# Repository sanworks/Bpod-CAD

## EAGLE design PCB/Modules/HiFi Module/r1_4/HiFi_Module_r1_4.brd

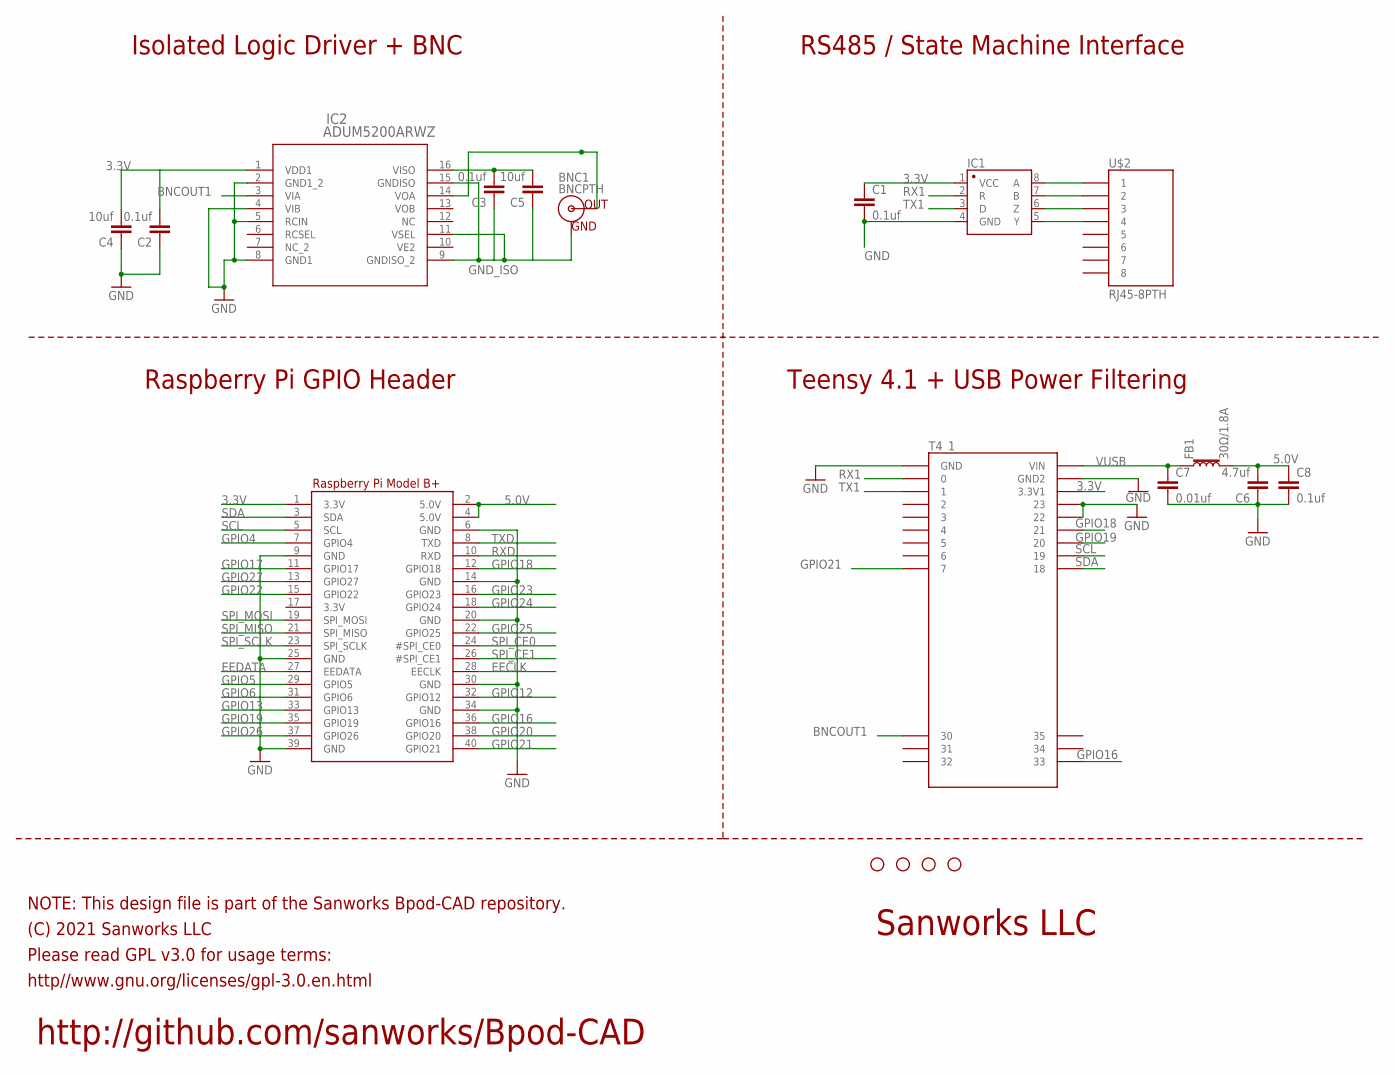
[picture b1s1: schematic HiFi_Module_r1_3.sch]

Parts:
BNC1: BNCPTH; BNC
C1, C2, C3, C8: 0.1uf; 0805
C4, C5: 10uf; 1206@2
C6: 4.7uf; 1206@2
C7: 0.01uf; 0805
FB1: 30Ω/1.8A; 0603
H1, H2, H3, H4: STAND-OFF
IC1: SN65HVD31DR; SO08
IC2: ADUM5200ARWZ; RW_16
RPI1: RASPBERRYPI_BPLUS_IDC; 2X20
T4_1: TEENSY4.1_FORAUDIO
U$2: RJ45-8PTH; RJ45-8

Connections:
3.3V: C1.1, C2.2, C4.2, IC1.1 (VCC), IC2.1 (VDD1), RPI1.1 (3.3V), T4_1.3V3_LO (3.3V1)
5.0V: C6.2, C8.1, FB1.2, RPI1.2 (5.0V), RPI1.4 (5.0V)
BNCOUT1: IC2.3 (VIA), T4_1.30
EECLK: RPI1.28 (EECLK)
EEDATA: RPI1.27 (EEDATA)
GND: C1.2, C2.1, C4.1, C6.1, C7.2, C8.2, IC1.4 (GND), IC2.2 (GND1_2), IC2.4 (VIB), IC2.5 (RCIN), IC2.8 (GND1), RPI1.6 (GND), RPI1.9 (GND), RPI1.14 (GND), RPI1.20 (GND), RPI1.25 (GND), RPI1.30 (GND), RPI1.34 (GND), RPI1.39 (GND), T4_1.22/A8 (22), T4_1.23/A9 (23), T4_1.AGND (GND), T4_1.GND (GND1); also elsewhere on the board
GND_ISO: BNC1.GND, C3.1, C5.1, IC2.9 (GNDISO_2), IC2.11 (VSEL), IC2.15 (GNDISO); also elsewhere on the board
GPIO4: RPI1.7 (GPIO4)
GPIO5: RPI1.29 (GPIO5)
GPIO6: RPI1.31 (GPIO6)
GPIO12: RPI1.32 (GPIO12)
GPIO13: RPI1.33 (GPIO13)
GPIO16: RPI1.36 (GPIO16), T4_1.33
GPIO17: RPI1.11 (GPIO17)
GPIO18: RPI1.12 (GPIO18), T4_1.21/A7 (21)
GPIO19: RPI1.35 (GPIO19), T4_1.20/A6 (20)
GPIO20: RPI1.38 (GPIO20)
GPIO21: RPI1.40 (GPIO21), T4_1.7
GPIO22: RPI1.15 (GPIO22)
GPIO23: RPI1.16 (GPIO23)
GPIO24: RPI1.18 (GPIO24)
GPIO25: RPI1.22 (GPIO25)
GPIO26: RPI1.37 (GPIO26)
GPIO27: RPI1.13 (GPIO27)
unnamed: IC1.6 (Z), U$2.3
unnamed: IC1.8 (A), U$2.1
unnamed: IC1.5 (Y), U$2.4
unnamed: IC1.7 (B), U$2.2
unnamed: C3.2, C5.2, IC2.16 (VISO)
unnamed 29: BNC1.S (OUT), IC2.14 (VOA); also elsewhere on the board
RX1: IC1.2 (R), T4_1.0/RX (0)
RXD: RPI1.10 (RXD)
SCL: RPI1.5 (SCL), T4_1.19/A5/SCL (19)
SDA: RPI1.3 (SDA), T4_1.18/A4/SDA (18)
SPI_CE0: RPI1.24 (#SPI_CE0)
SPI_CE1: RPI1.26 (#SPI_CE1)
SPI_MISO: RPI1.21 (SPI_MISO)
SPI_MOSI: RPI1.19 (SPI_MOSI)
SPI_SCLK: RPI1.23 (SPI_SCLK)
TX1: IC1.3 (D), T4_1.1/TX (1)
TXD: RPI1.8 (TXD)
VUSB: C7.1, FB1.1, T4_1.VIN

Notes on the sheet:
http://github.com/sanworks/Bpod-CAD
NOTE: This design file is part of the Sanworks Bpod-CAD repository.
(C) 2021 Sanworks LLC
http//www.gnu.org/licenses/gpl-3.0.en.html
Please read GPL v3.0 for usage terms:
Sanworks LLC
Isolated Logic Driver + BNC
RS485 / State Machine Interface
Raspberry Pi GPIO Header
Teensy 4.1 + USB Power Filtering

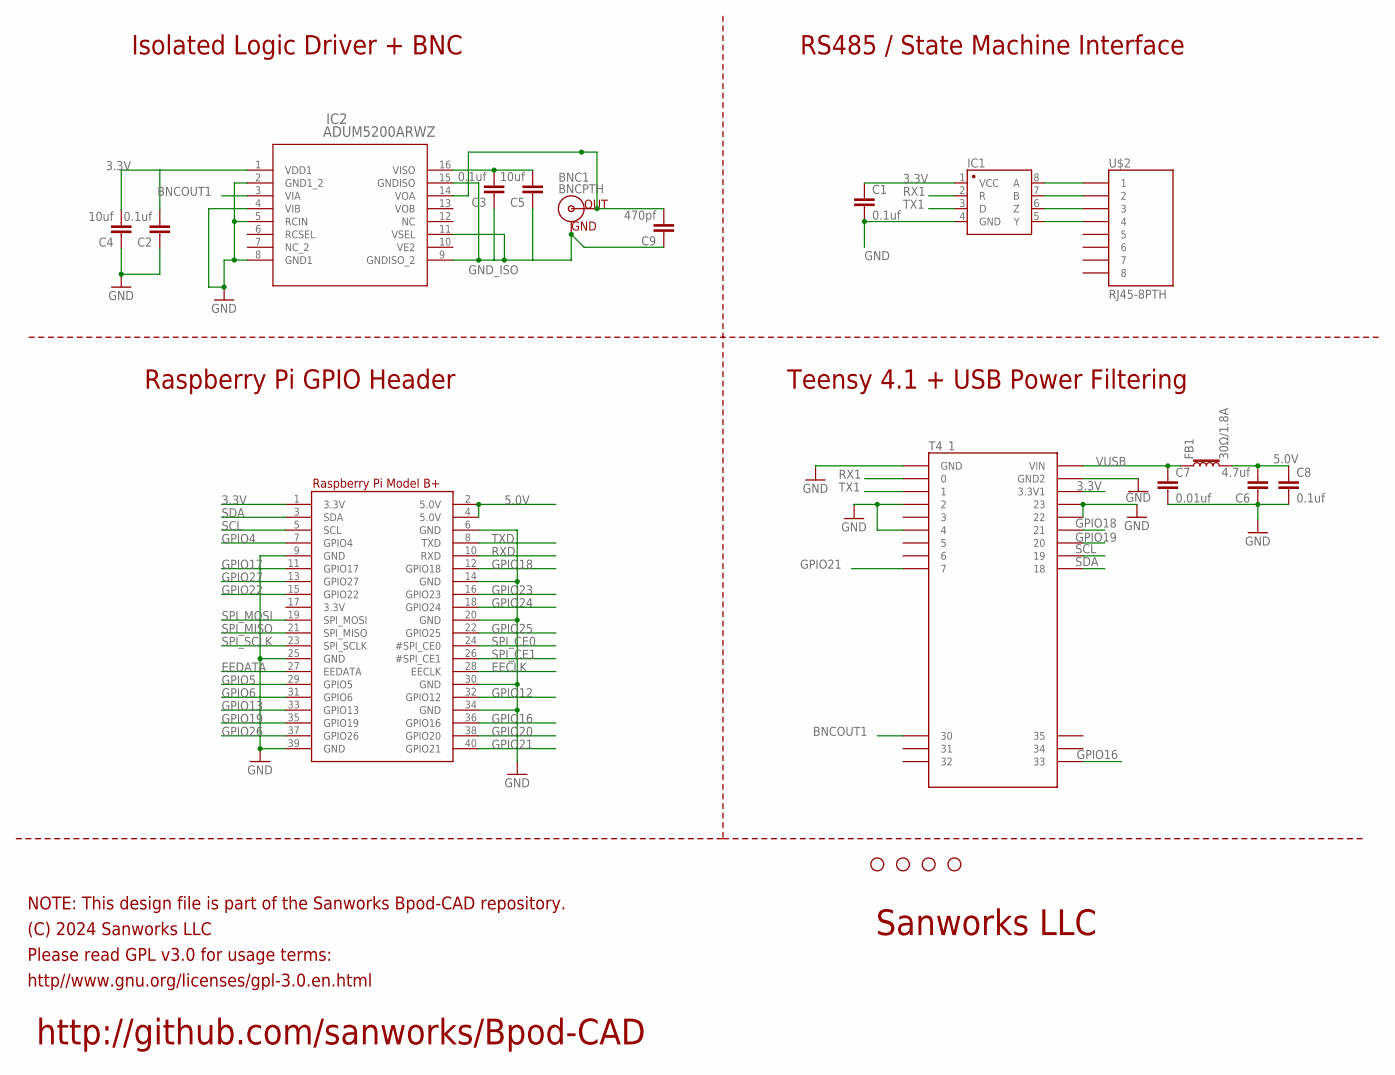
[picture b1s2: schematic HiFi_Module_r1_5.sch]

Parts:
BNC1: BNCPTH; BNC
C1, C2, C3, C8: 0.1uf; 0805
C4, C5: 10uf; 1206@2
C6: 4.7uf; 1206@2
C7: 0.01uf; 0805
C9: 470pf; 0805
FB1: 30Ω/1.8A; 0603
H1, H2, H3, H4: STAND-OFF
IC1: SN65HVD31DR; SO08
IC2: ADUM5200ARWZ; RW_16
RPI1: RASPBERRYPI_BPLUS_IDC; 2X20
T4_1: TEENSY4.1_FORAUDIO
U$2: RJ45-8PTH; RJ45-8

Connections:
3.3V: C1.1, C2.2, C4.2, IC1.1 (VCC), IC2.1 (VDD1), RPI1.1 (3.3V), T4_1.3V3_LO (3.3V1)
5.0V: C6.2, C8.1, FB1.2, RPI1.2 (5.0V), RPI1.4 (5.0V)
BNCOUT1: IC2.3 (VIA), T4_1.30
EECLK: RPI1.28 (EECLK)
EEDATA: RPI1.27 (EEDATA)
GND: C1.2, C2.1, C4.1, C6.1, C7.2, C8.2, IC1.4 (GND), IC2.2 (GND1_2), IC2.4 (VIB), IC2.5 (RCIN), IC2.8 (GND1), RPI1.6 (GND), RPI1.9 (GND), RPI1.14 (GND), RPI1.20 (GND), RPI1.25 (GND), RPI1.30 (GND), RPI1.34 (GND), RPI1.39 (GND), T4_1.2, T4_1.4, T4_1.22/A8 (22), T4_1.23/A9 (23), T4_1.AGND (GND), T4_1.GND (GND1); also elsewhere on the board
GND_ISO: BNC1.GND, C3.1, C5.1, C9.1, IC2.9 (GNDISO_2), IC2.11 (VSEL), IC2.15 (GNDISO)
GPIO4: RPI1.7 (GPIO4)
GPIO5: RPI1.29 (GPIO5)
GPIO6: RPI1.31 (GPIO6)
GPIO12: RPI1.32 (GPIO12)
GPIO13: RPI1.33 (GPIO13)
GPIO16: RPI1.36 (GPIO16), T4_1.33
GPIO17: RPI1.11 (GPIO17)
GPIO18: RPI1.12 (GPIO18), T4_1.21/A7 (21)
GPIO19: RPI1.35 (GPIO19), T4_1.20/A6 (20)
GPIO20: RPI1.38 (GPIO20)
GPIO21: RPI1.40 (GPIO21), T4_1.7
GPIO22: RPI1.15 (GPIO22)
GPIO23: RPI1.16 (GPIO23)
GPIO24: RPI1.18 (GPIO24)
GPIO25: RPI1.22 (GPIO25)
GPIO26: RPI1.37 (GPIO26)
GPIO27: RPI1.13 (GPIO27)
unnamed: IC1.6 (Z), U$2.3
unnamed: IC1.8 (A), U$2.1
unnamed: IC1.5 (Y), U$2.4
unnamed: IC1.7 (B), U$2.2
unnamed: C3.2, C5.2, IC2.16 (VISO)
unnamed: BNC1.S (OUT), C9.2, IC2.14 (VOA)
RX1: IC1.2 (R), T4_1.0/RX (0)
RXD: RPI1.10 (RXD)
SCL: RPI1.5 (SCL), T4_1.19/A5/SCL (19)
SDA: RPI1.3 (SDA), T4_1.18/A4/SDA (18)
SPI_CE0: RPI1.24 (#SPI_CE0)
SPI_CE1: RPI1.26 (#SPI_CE1)
SPI_MISO: RPI1.21 (SPI_MISO)
SPI_MOSI: RPI1.19 (SPI_MOSI)
SPI_SCLK: RPI1.23 (SPI_SCLK)
TX1: IC1.3 (D), T4_1.1/TX (1)
TXD: RPI1.8 (TXD)
VUSB: C7.1, FB1.1, T4_1.VIN

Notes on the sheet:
http://github.com/sanworks/Bpod-CAD
NOTE: This design file is part of the Sanworks Bpod-CAD repository.
(C) 2024 Sanworks LLC
http//www.gnu.org/licenses/gpl-3.0.en.html
Please read GPL v3.0 for usage terms:
Sanworks LLC
Isolated Logic Driver + BNC
RS485 / State Machine Interface
Raspberry Pi GPIO Header
Teensy 4.1 + USB Power Filtering

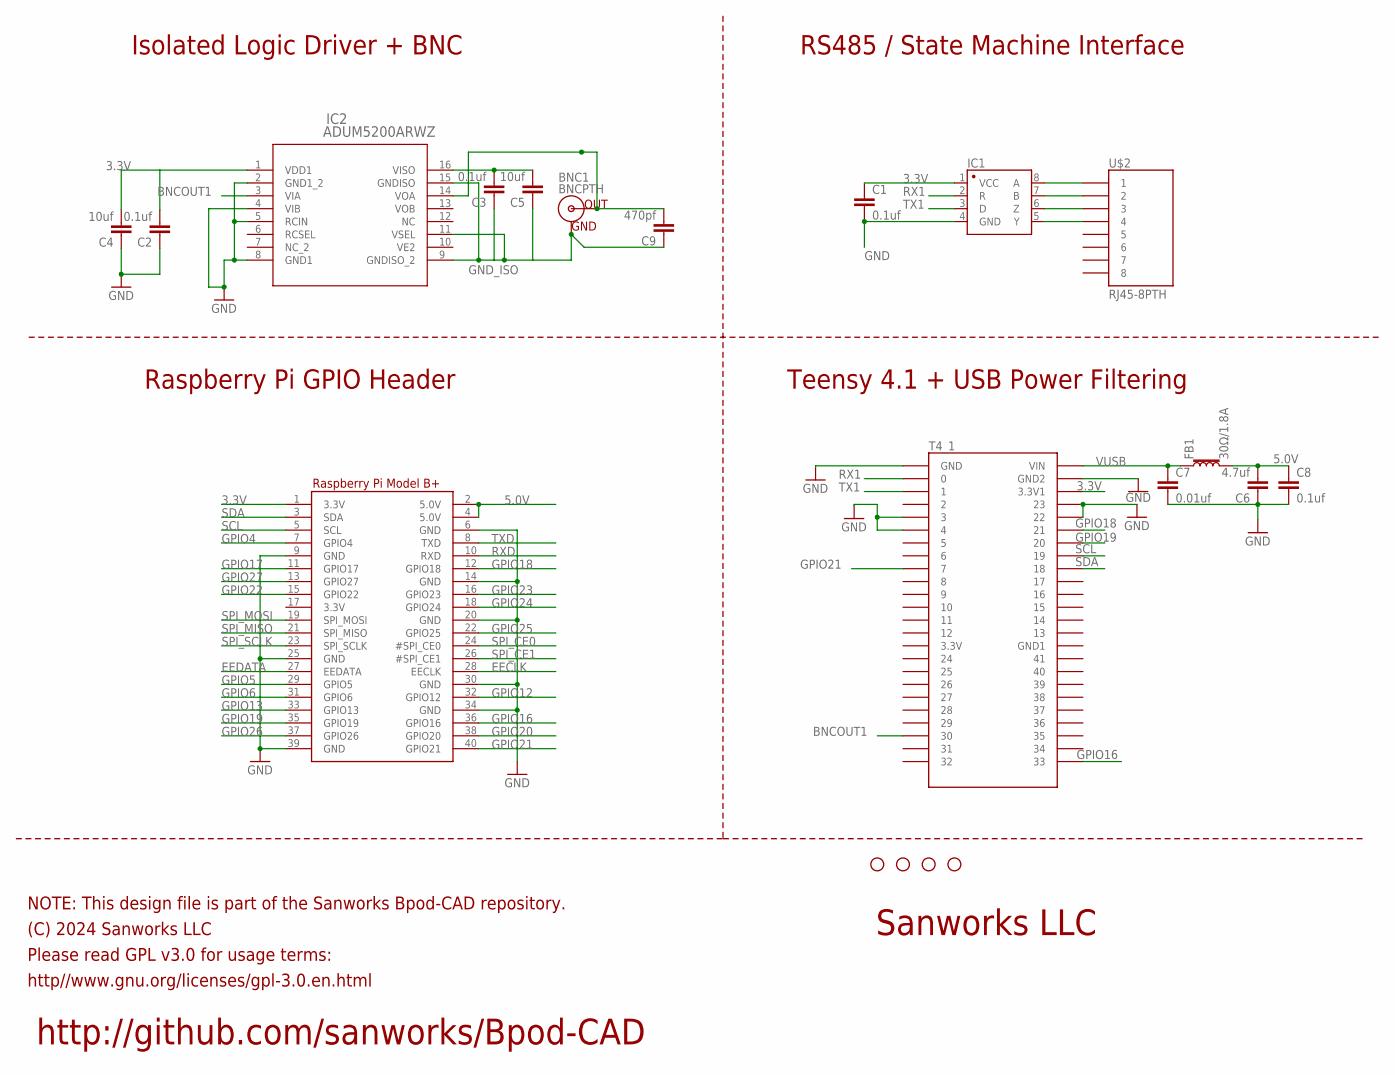
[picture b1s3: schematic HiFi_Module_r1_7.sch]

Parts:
BNC1: BNCPTH; BNC
C1, C2, C3, C8: 0.1uf; 0805
C4, C5: 10uf; 1206@2
C6: 4.7uf; 1206@2
C7: 0.01uf; 0805
C9: 470pf; 0805
FB1: 30Ω/1.8A; 0603
H1, H2, H3, H4: STAND-OFF
IC1: SN65HVD31DR; SO08
IC2: ADUM5200ARWZ; RW_16
RPI1: RASPBERRYPI_BPLUS_IDC; 2X20
T4_1: TEENSY4.1_SIDESONLY
U$2: RJ45-8PTH; RJ45-8

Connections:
3.3V: C1.1, C2.2, C4.2, IC1.1 (VCC), IC2.1 (VDD1), RPI1.1 (3.3V), T4_1.3V3_LO (3.3V1)
5.0V: C6.2, C8.1, FB1.2, RPI1.2 (5.0V), RPI1.4 (5.0V)
BNCOUT1: IC2.3 (VIA), T4_1.30
EECLK: RPI1.28 (EECLK)
EEDATA: RPI1.27 (EEDATA)
GND: C1.2, C2.1, C4.1, C6.1, C7.2, C8.2, IC1.4 (GND), IC2.2 (GND1_2), IC2.4 (VIB), IC2.5 (RCIN), IC2.8 (GND1), RPI1.6 (GND), RPI1.9 (GND), RPI1.14 (GND), RPI1.20 (GND), RPI1.25 (GND), RPI1.30 (GND), RPI1.34 (GND), RPI1.39 (GND), T4_1.3, T4_1.4, T4_1.22/A8 (22), T4_1.23/A9 (23), T4_1.AGND (GND), T4_1.GND1 (GND2); also elsewhere on the board
GND_ISO: BNC1.GND, C3.1, C5.1, C9.1, IC2.9 (GNDISO_2), IC2.11 (VSEL), IC2.15 (GNDISO)
GPIO4: RPI1.7 (GPIO4)
GPIO5: RPI1.29 (GPIO5)
GPIO6: RPI1.31 (GPIO6)
GPIO12: RPI1.32 (GPIO12)
GPIO13: RPI1.33 (GPIO13)
GPIO16: RPI1.36 (GPIO16), T4_1.33
GPIO17: RPI1.11 (GPIO17)
GPIO18: RPI1.12 (GPIO18), T4_1.21/A7 (21)
GPIO19: RPI1.35 (GPIO19), T4_1.20/A6 (20)
GPIO20: RPI1.38 (GPIO20)
GPIO21: RPI1.40 (GPIO21), T4_1.7
GPIO22: RPI1.15 (GPIO22)
GPIO23: RPI1.16 (GPIO23)
GPIO24: RPI1.18 (GPIO24)
GPIO25: RPI1.22 (GPIO25)
GPIO26: RPI1.37 (GPIO26)
GPIO27: RPI1.13 (GPIO27)
unnamed: IC1.6 (Z), U$2.3
unnamed: IC1.8 (A), U$2.1
unnamed: IC1.5 (Y), U$2.4
unnamed: IC1.7 (B), U$2.2
unnamed: C3.2, C5.2, IC2.16 (VISO)
unnamed: BNC1.S (OUT), C9.2, IC2.14 (VOA)
RX1: IC1.2 (R), T4_1.0/RX (0)
RXD: RPI1.10 (RXD)
SCL: RPI1.5 (SCL), T4_1.19/A5/SCL (19)
SDA: RPI1.3 (SDA), T4_1.18/A4/SDA (18)
SPI_CE0: RPI1.24 (#SPI_CE0)
SPI_CE1: RPI1.26 (#SPI_CE1)
SPI_MISO: RPI1.21 (SPI_MISO)
SPI_MOSI: RPI1.19 (SPI_MOSI)
SPI_SCLK: RPI1.23 (SPI_SCLK)
TX1: IC1.3 (D), T4_1.1/TX (1)
TXD: RPI1.8 (TXD)
VUSB: C7.1, FB1.1, T4_1.VIN

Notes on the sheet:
http://github.com/sanworks/Bpod-CAD
NOTE: This design file is part of the Sanworks Bpod-CAD repository.
(C) 2024 Sanworks LLC
http//www.gnu.org/licenses/gpl-3.0.en.html
Please read GPL v3.0 for usage terms:
Sanworks LLC
Isolated Logic Driver + BNC
RS485 / State Machine Interface
Raspberry Pi GPIO Header
Teensy 4.1 + USB Power Filtering

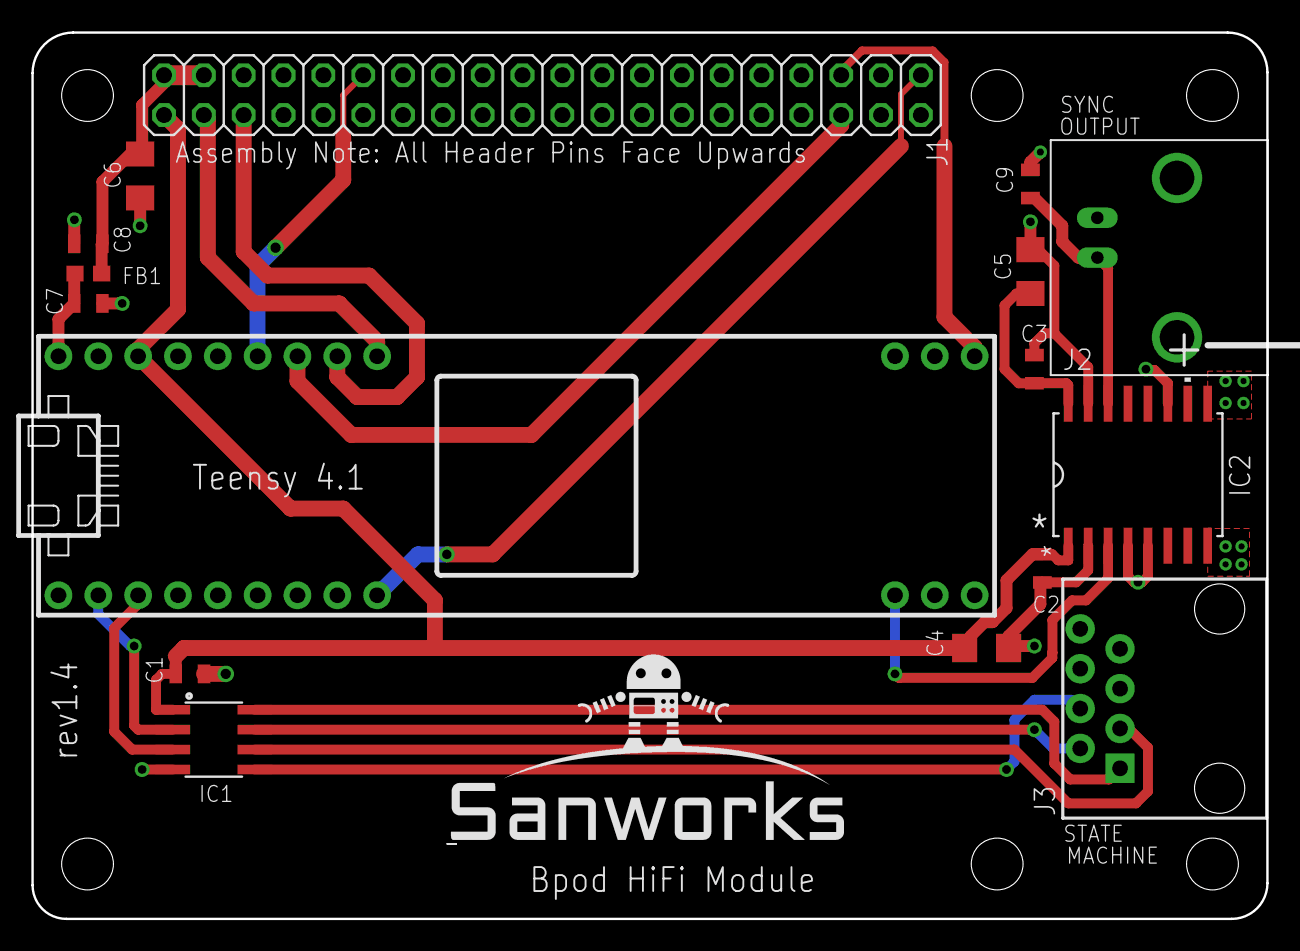
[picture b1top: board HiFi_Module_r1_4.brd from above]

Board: 2 copper layers, 78.7 x 56.5 mm, 23 parts (0 on the bottom side), 20 nets.

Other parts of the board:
H5, H6: STAND-OFF
U$1: SANWORKS_LOGO

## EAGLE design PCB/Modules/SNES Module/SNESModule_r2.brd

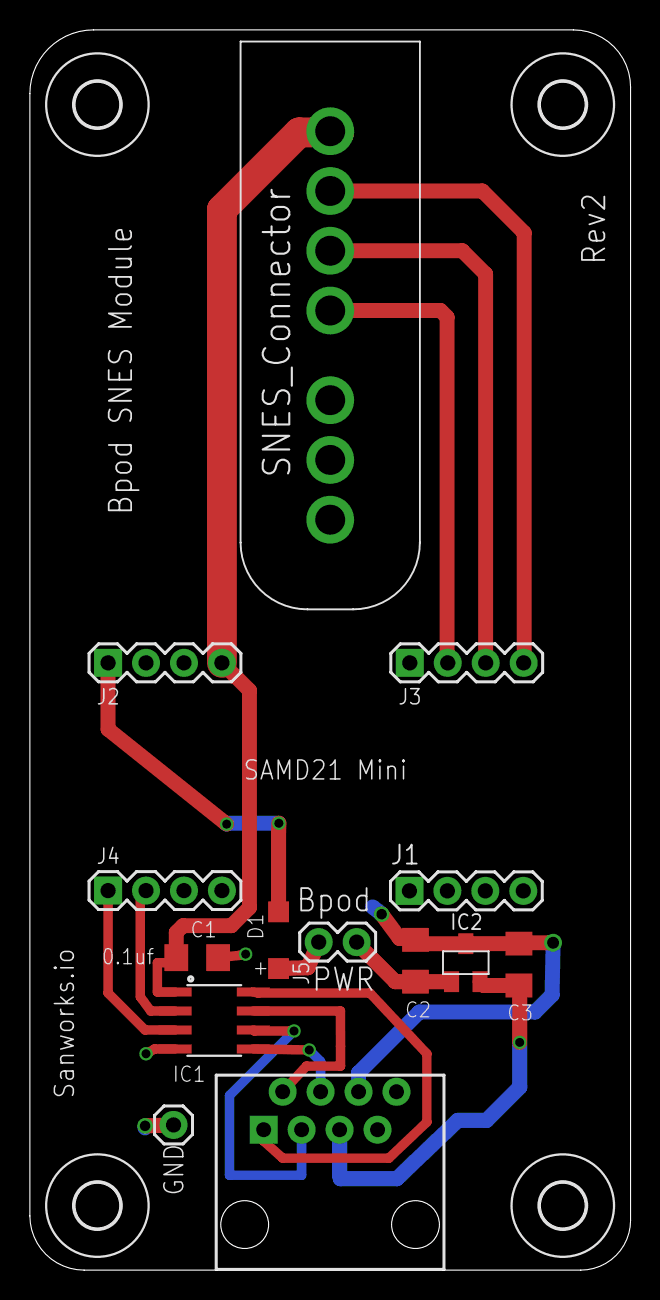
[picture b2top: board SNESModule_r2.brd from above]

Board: 2 copper layers, 40.2 x 83.0 mm, 18 parts (0 on the bottom side), 15 nets.

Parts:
C1, C2, C3: 0.1uf; 1206
D1: MBR0520LT; SOD123
H1, H2, H3, H4: MOUNT-HOLE3.0; 3,0
IC1: SN65HVD31DR; SO08
IC2: LM3480-5.0; SOT-23-3
J1, J2, J3, J4: 1X04
J5: 1X02
J7: 1X01
U$1: RJ45-8PTH; RJ45-8
U$2: SNES_CONNECTOR

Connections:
5V: D1.C, J2.1
GND: C1.2, C2.1, C3.1, IC1.4, IC2.3, J4.4, J7.1, U$1.6, U$2.GND
unnamed: J3.2, U$2.DATA
unnamed: J3.3, U$2.LATCH
unnamed: J3.4, U$2.CLOCK
unnamed: IC1.3, J4.1
unnamed: C2.2, IC2.1, J5.1
unnamed: IC1.2, J4.2
unnamed: IC1.8, U$1.1
unnamed: IC1.7, U$1.2
unnamed: IC1.6, U$1.3
unnamed: IC1.5, U$1.4
unnamed: D1.A, J5.2
unnamed: C3.2, IC2.2, U$1.5
VCC: C1.1, IC1.1, J2.4, U$2.V+

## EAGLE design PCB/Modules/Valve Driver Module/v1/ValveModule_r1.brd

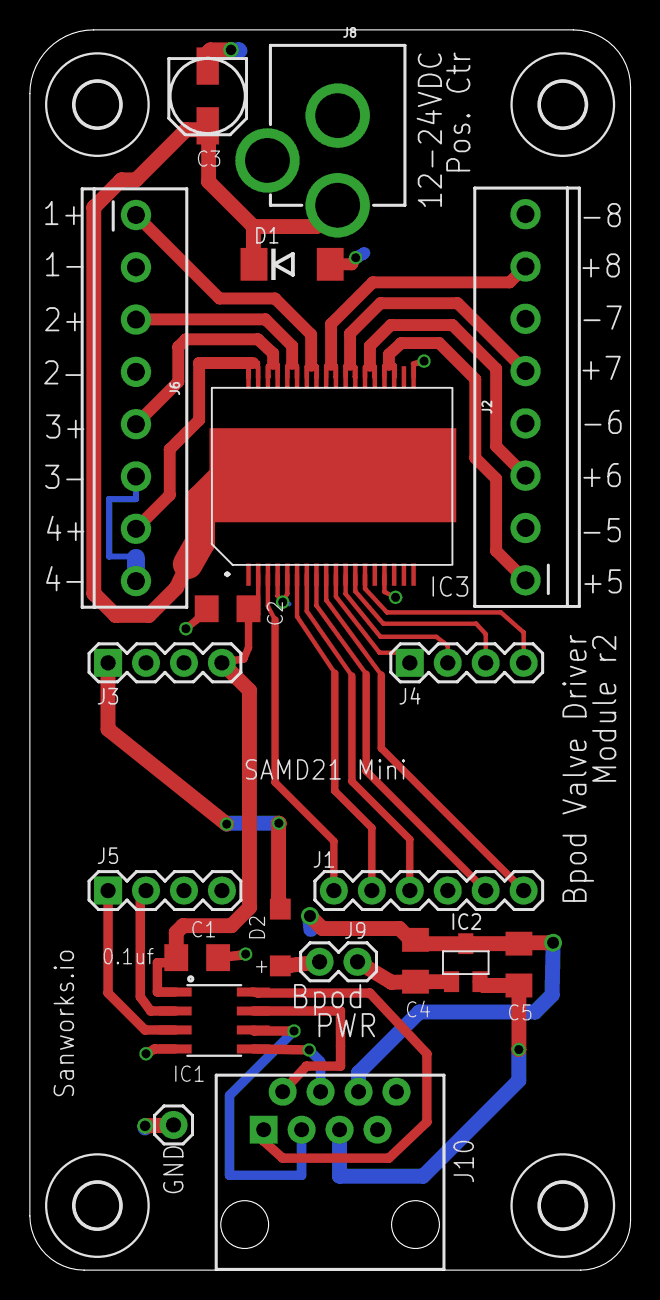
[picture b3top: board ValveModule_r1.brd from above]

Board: 2 copper layers, 40.2 x 83.0 mm, 24 parts (0 on the bottom side), 31 nets.

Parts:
C1, C2, C4, C5: 0.1uf; 1206
C3: EEE-FK1H100UR
D1: DO214AA
D2: MBR0520LT; SOD123
H1, H2, H3, H4: MOUNT-HOLE3.0; 3,0
IC1: SN65HVD31DR; SO08
IC2: LM3480-5.0; SOT-23-3
IC3: ISO1H811G
J1: 1X06
J2, J6: SCREWTERMINAL-3.5MM-8
J3, J4, J5: 1X04
J7: 1X01
J8: POWER_JACK; POWER_JACK_PTH
J9: 1X02
J10: RJ45-8PTH; RJ45-8

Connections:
5V: D2.C, J3.1
GND: C1.2, C2.1, C4.1, C5.1, IC1.4, IC2.3, IC3.P$4, IC3.P$5, IC3.P$15, J5.4, J7.1, J10.6
GNDBB: C3.CATHODE, D1.A, IC3.P$19, J2.2, J2.4, J2.6, J2.8, J6.2, J6.4, J6.6, J6.8, J8.GND, J8.GNDBREAK
unnamed: IC3.P$35, IC3.P$36, J6.7
unnamed: IC3.P$3, J1.1
unnamed: IC3.P$6, J1.2
unnamed: IC1.3, J5.1
unnamed: IC3.P$7, J1.3
unnamed: IC1.2, J5.2
unnamed: IC1.8, J10.1
unnamed: IC1.7, J10.2
unnamed: IC1.6, J10.3
unnamed: IC1.5, J10.4
unnamed: IC3.P$8, J1.5
unnamed: IC3.P$9, J1.6
unnamed: IC3.P$10, J4.1
unnamed: IC3.P$11, J4.2
unnamed: IC3.P$12, J4.3
unnamed: IC3.P$13, J4.4
unnamed: IC3.P$33, IC3.P$34, J6.5
unnamed: IC3.P$31, IC3.P$32, J6.3
unnamed: IC3.P$29, IC3.P$30, J6.1
unnamed: IC3.P$27, IC3.P$28, J2.7
unnamed: IC3.P$25, IC3.P$26, J2.5
unnamed: IC3.P$23, IC3.P$24, J2.3
unnamed: IC3.P$21, IC3.P$22, J2.1
unnamed: C5.2, IC2.2, J10.5
unnamed: C4.2, IC2.1, J9.1
unnamed: D2.A, J9.2
VBB: C3.ANODE, D1.C, IC3.VBB, J8.PWR
VCC: C1.1, C2.2, IC1.1, IC3.P$2, J3.4

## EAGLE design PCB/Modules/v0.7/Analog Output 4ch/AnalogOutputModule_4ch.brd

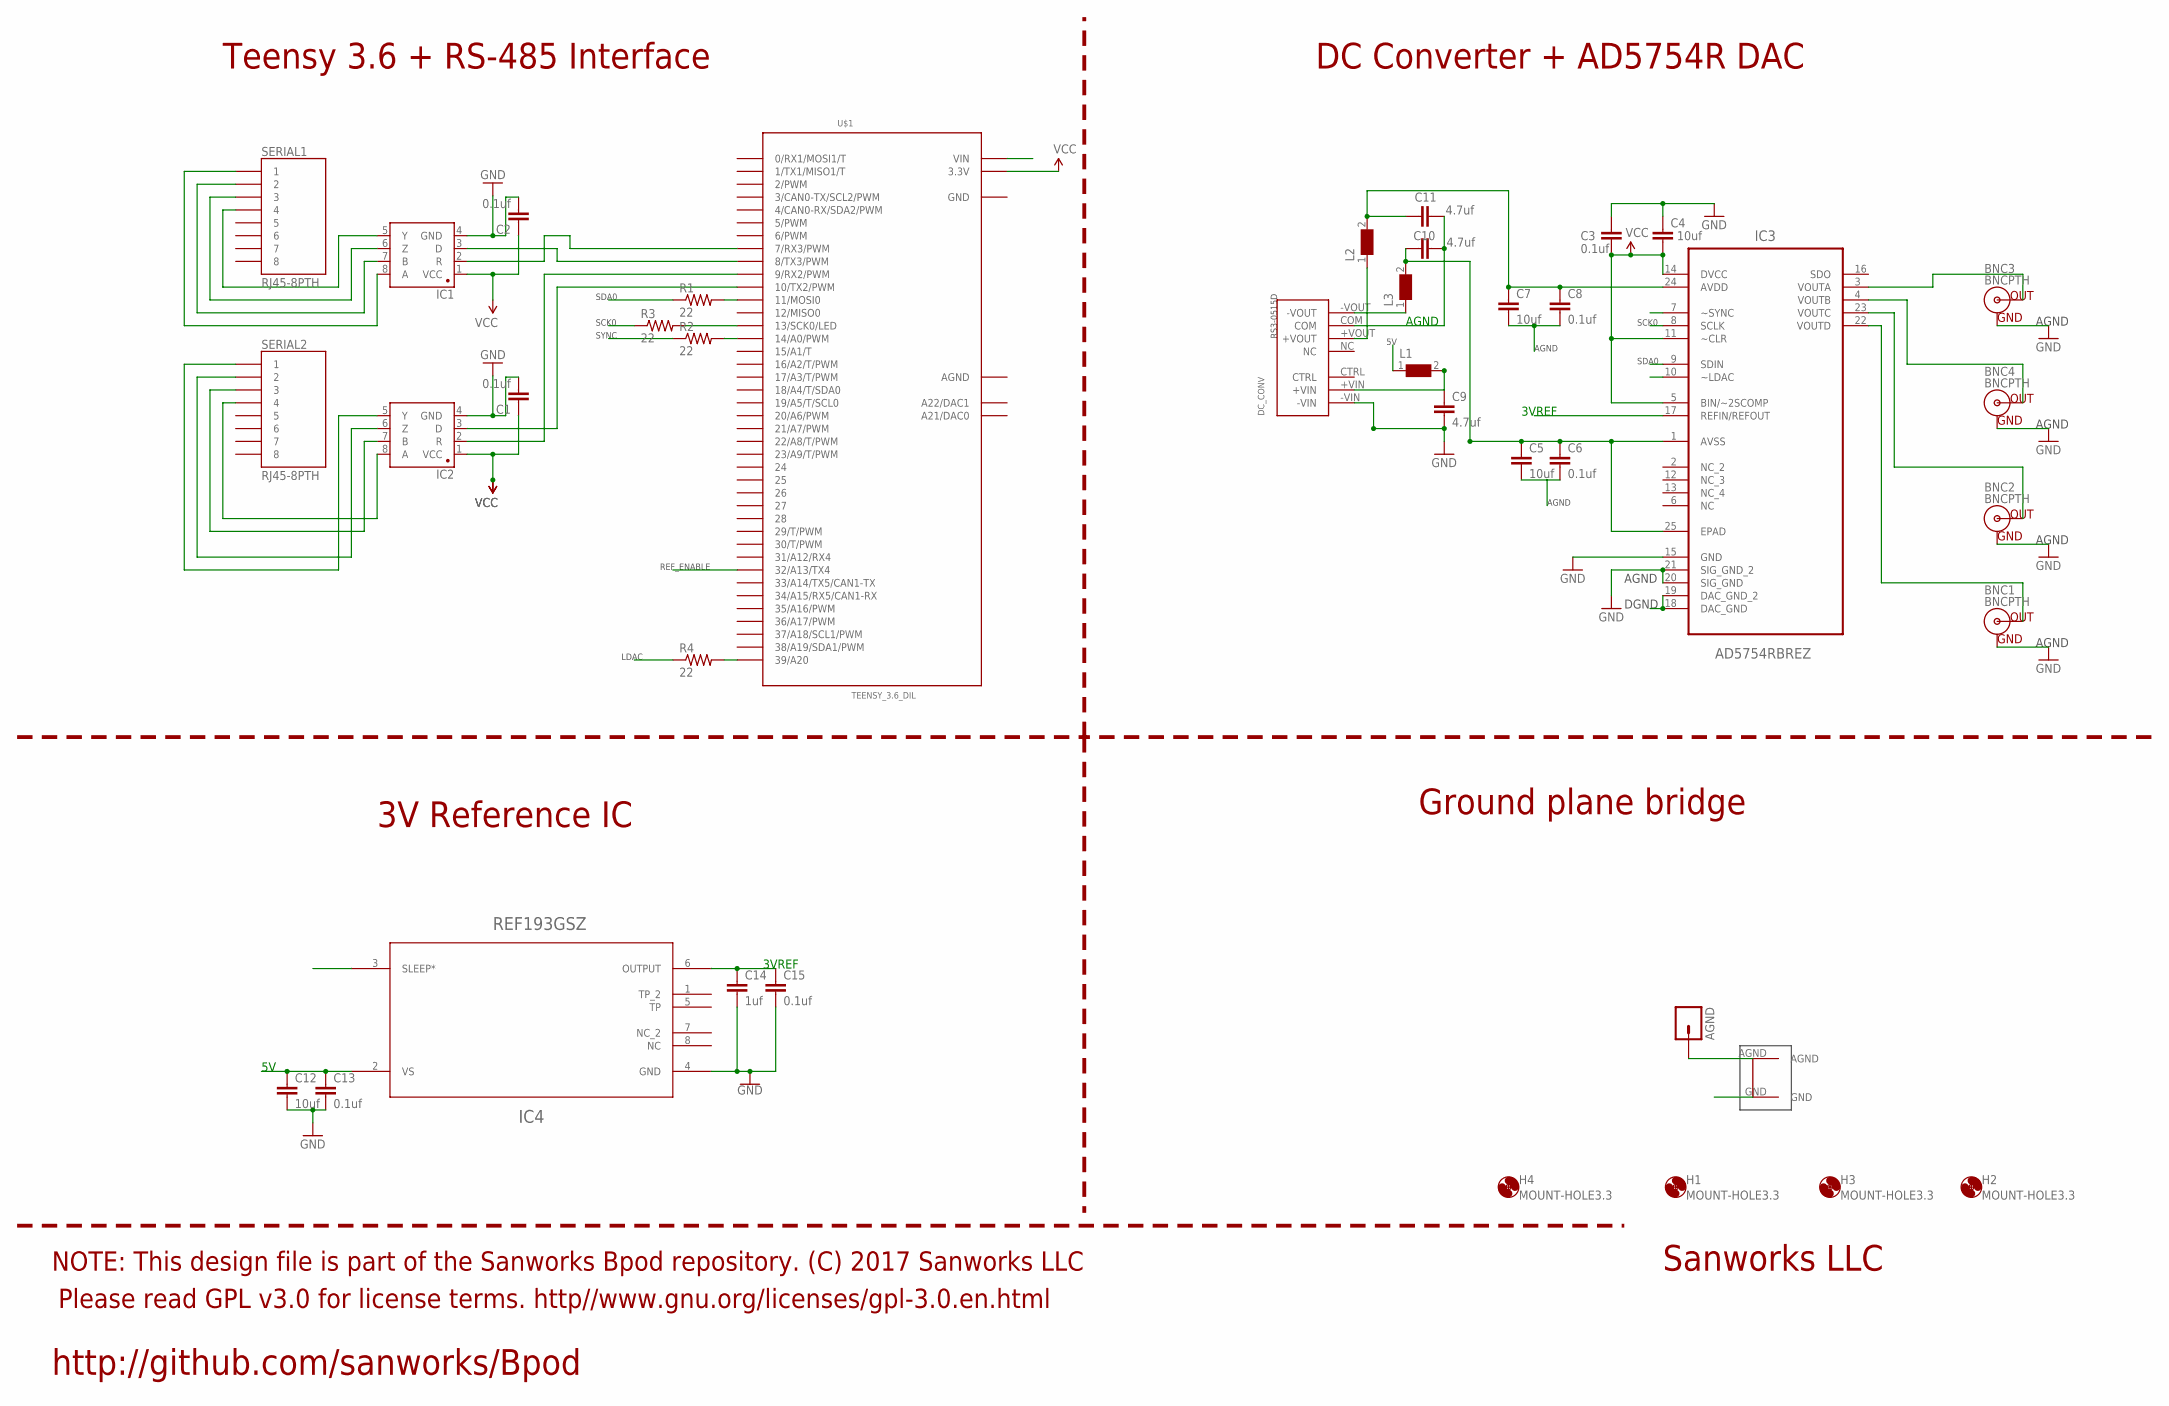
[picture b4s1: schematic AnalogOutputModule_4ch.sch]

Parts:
AGND: M01PTH; 1X01
BNC1, BNC2, BNC3, BNC4: BNCPTH; BNC
C1, C2: 0.1uf; 1206
C3, C6, C8, C13, C15: 0.1uf; 0603-CAP
C4, C5, C7, C12: 10uf; 1206
C9, C10, C11: 4.7uf; 1206
C14: 1uf; 1206
DC_CONV: RS3-0515D
H1, H2, H3, H4: MOUNT-HOLE3.3; 3,3
IC1, IC2: SN65HVD31DR; SO08
IC3: AD5754RBREZ; SOP65P640X120-25N
IC4: REF193GSZ; R_8
L1, L2, L3: WE-CBF-742792118_1206; 1206
R1, R2, R3, R4: 22; 1206
SERIAL1, SERIAL2: RJ45-8PTH; RJ45-8
U$1: TEENSY_3.6_DIL
U$6: GNDPLANESHRT

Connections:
3VREF: C14.1, C15.1, IC3.17 (REFIN/REFOUT), IC4.6 (OUTPUT)
5V: C3.2, C4.2, C12.1, C13.1, IC3.5 (BIN/~2SCOMP), IC3.11 (~CLR), IC3.14 (DVCC), IC4.2 (VS), L1.1, U$1.VIN
AGND: AGND.1, BNC1.GND, BNC2.GND, BNC3.GND, BNC4.GND, C5.2, C6.2, C7.2, C8.2, C10.1, C11.2, DC_CONV.COM, IC3.18 (DAC_GND), IC3.19 (DAC_GND_2), IC3.20 (SIG_GND), IC3.21 (SIG_GND_2), U$1.AGND, U$6.AGND
GND: C1.2, C2.2, C3.1, C4.1, C9.2, C12.2, C13.2, C14.2, C15.2, DC_CONV.-VIN, IC1.4 (GND), IC2.4 (GND), IC3.15 (GND), IC4.4 (GND), U$1.GND, U$1.GND1 (GND), U$6.GND
LDAC: IC3.10 (~LDAC), R4.1
unnamed: IC1.3 (D), U$1.8 (8/TX3/PWM)
unnamed: IC1.2 (R), U$1.7 (7/RX3/PWM)
unnamed: IC2.8 (A), SERIAL2.4
unnamed: IC2.7 (B), SERIAL2.3
unnamed: IC2.6 (Z), SERIAL2.2
unnamed: IC2.5 (Y), SERIAL2.1
unnamed: IC2.3 (D), U$1.10 (10/TX2/PWM)
unnamed: IC2.2 (R), U$1.9 (9/RX2/PWM)
unnamed: BNC3.S (OUT), IC3.3 (VOUTA)
unnamed: BNC4.S (OUT), IC3.4 (VOUTB)
unnamed: BNC2.S (OUT), IC3.23 (VOUTC)
unnamed: BNC1.S (OUT), IC3.22 (VOUTD)
unnamed: R1.2, U$1.11 (11/MOSI0)
unnamed: R3.2, U$1.13 (13/SCK0/LED)
unnamed: DC_CONV.-VOUT, L3.1
unnamed: DC_CONV.+VOUT, L2.1
unnamed: R2.2, U$1.14/A0 (14/A0/PWM)
unnamed: R4.2, U$1.39/A20
unnamed: IC1.8 (A), SERIAL1.1
unnamed: IC1.7 (B), SERIAL1.2
unnamed: IC1.6 (Z), SERIAL1.3
unnamed: IC1.5 (Y), SERIAL1.4
unnamed: C7.1, C8.1, C10.2, IC3.24 (AVDD), L2.2
unnamed: C9.1, DC_CONV.+VIN, L1.2
REF_ENABLE: IC4.3 (SLEEP*), U$1.32/A13 (32/A13/TX4)
SCK0: IC3.8 (SCLK), R3.1
SDA0: IC3.9 (SDIN), R1.1
SYNC: IC3.7 (~SYNC), R2.1
VCC: C1.1, C2.1, IC1.1 (VCC), IC2.1 (VCC), U$1.3.3V, U$1.3.3V3 (3.3V)
VSS: C5.1, C6.1, C11.1, IC3.1 (AVSS), IC3.25 (EPAD), L3.2

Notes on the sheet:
AGND
SCK0
SDA0
DGND
SYNC
LDAC
3VREF
REF_ENABLE
Teensy 3.6 + RS-485 Interface
DC Converter + AD5754R DAC
3V Reference IC
Ground plane bridge
Please read GPL v3.0 for license terms. http//www.gnu.org/licenses/gpl-3.0.en.html
NOTE: This design file is part of the Sanworks Bpod repository. (C) 2017 Sanworks LLC
Sanworks LLC
http://github.com/sanworks/Bpod

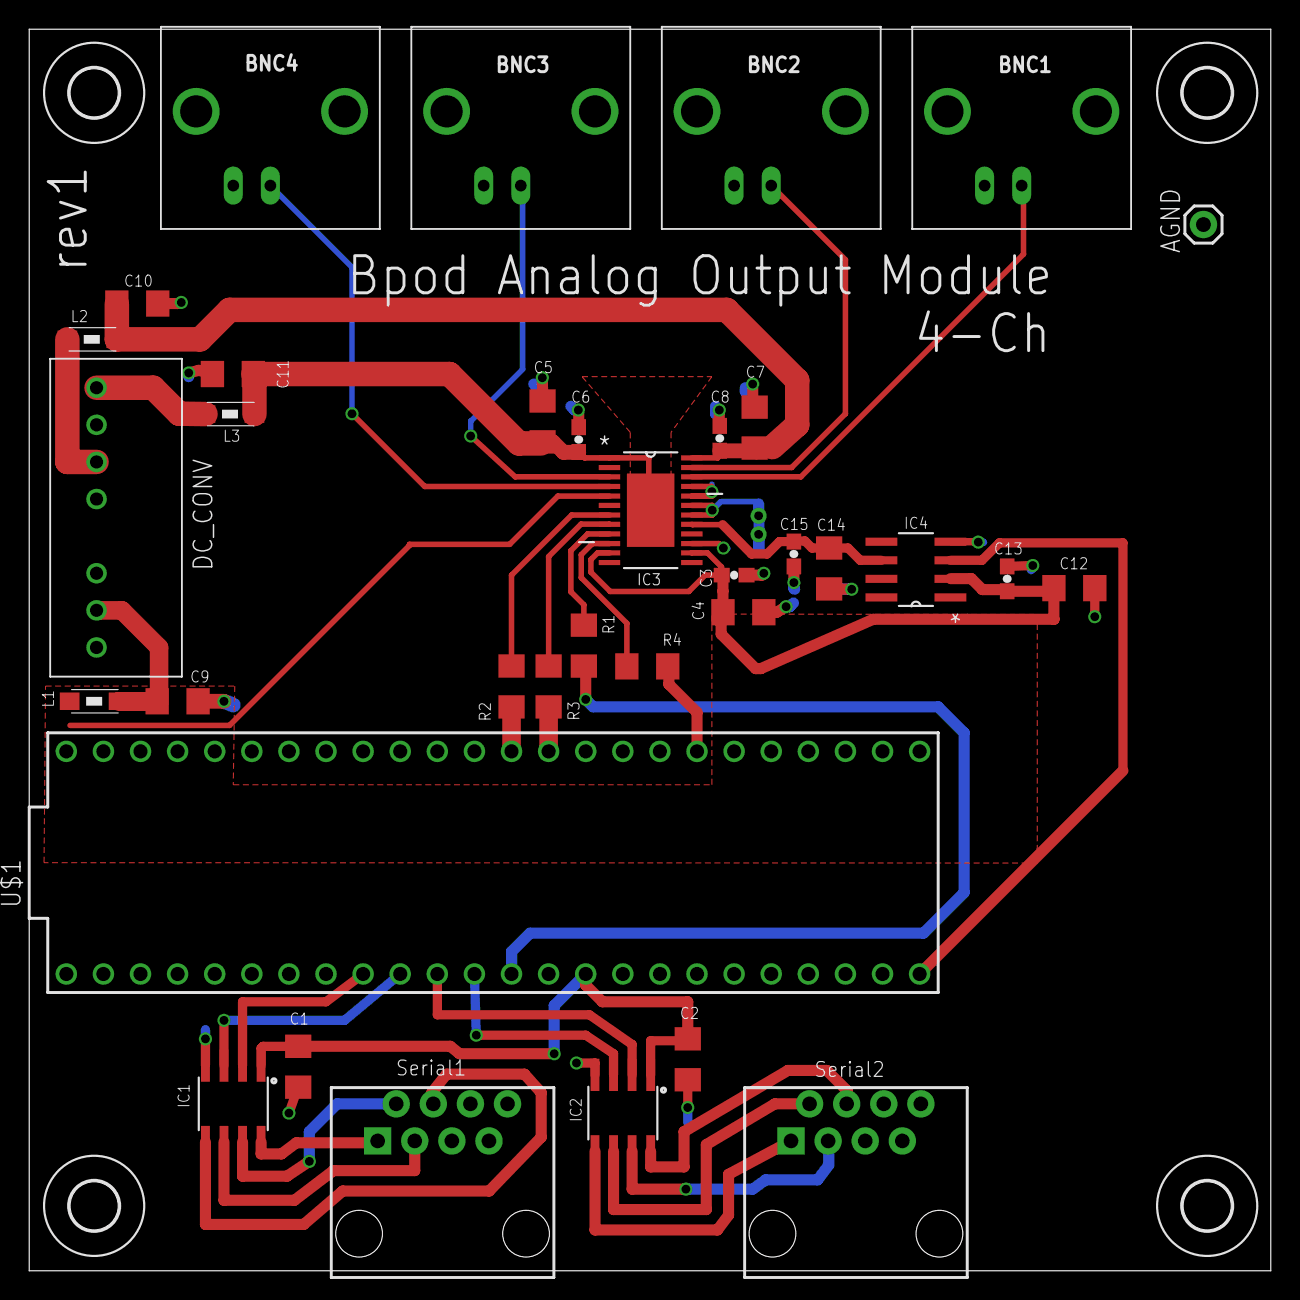
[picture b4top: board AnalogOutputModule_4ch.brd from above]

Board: 2 copper layers, 85.0 x 85.0 mm, 40 parts (0 on the bottom side), 35 nets.

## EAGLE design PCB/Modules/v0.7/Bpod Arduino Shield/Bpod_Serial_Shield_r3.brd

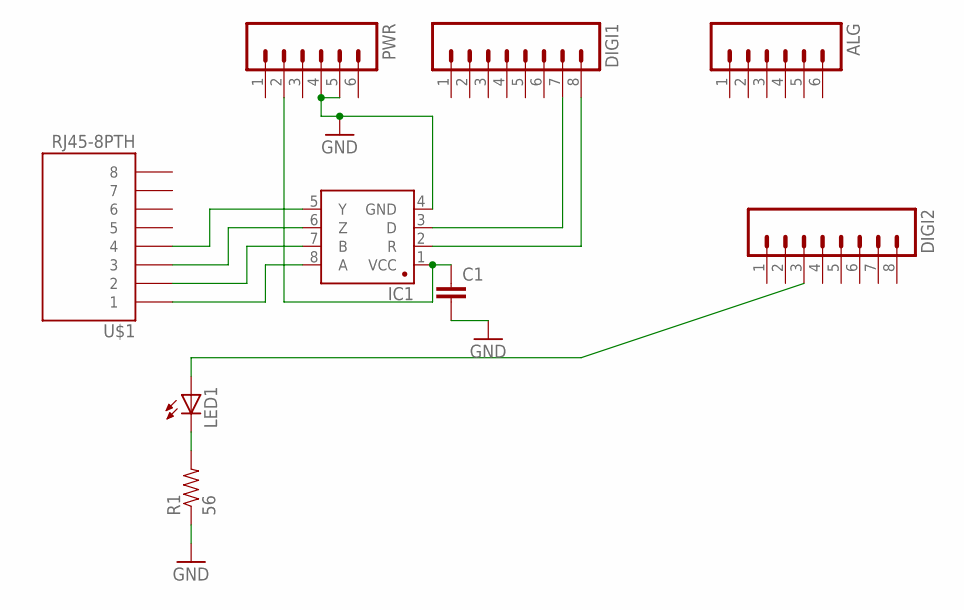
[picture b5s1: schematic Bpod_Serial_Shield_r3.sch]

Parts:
ALG: M06LONGPADS; 1X06_LONGPADS
C1: CAP1206; 1206
DIGI1, DIGI2: M08LONGPADS; 1X08_LONGPADS
IC1: SN65HVD31DR; SO08
LED1: LEDCHIPLED_1206; CHIPLED_1206
PWR: M06LONGPADS; 1X06_LONGPADS
R1: 56; 1206
U$1: RJ45-8PTH; RJ45-8

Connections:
GND: C1.2, IC1.4 (GND), PWR.4, PWR.5, R1.1
unnamed: C1.1, IC1.1 (VCC), PWR.2
unnamed: LED1.C, R1.2
unnamed: DIGI2.3, LED1.A
unnamed: DIGI1.7, IC1.3 (D)
unnamed: DIGI1.8, IC1.2 (R)
unnamed: IC1.8 (A), U$1.1
unnamed: IC1.7 (B), U$1.2
unnamed: IC1.6 (Z), U$1.3
unnamed: IC1.5 (Y), U$1.4

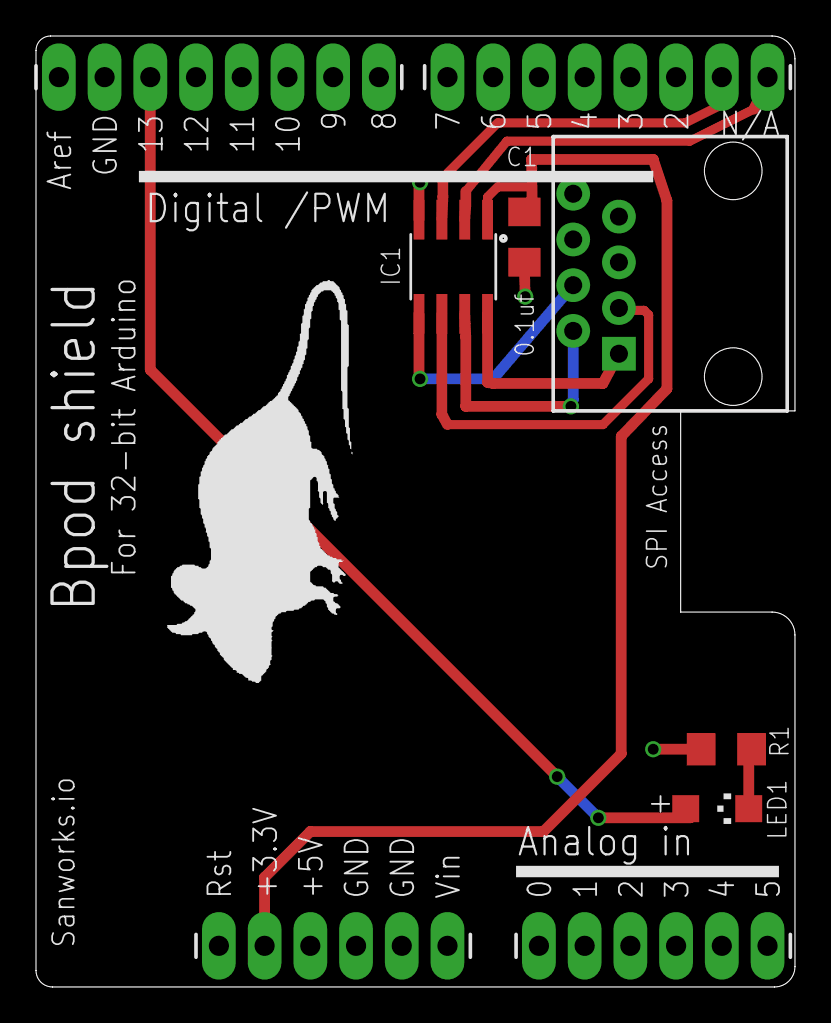
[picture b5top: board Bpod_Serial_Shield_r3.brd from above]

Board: 2 copper layers, 42.2 x 52.8 mm, 10 parts (0 on the bottom side), 10 nets.

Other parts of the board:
U$2: MOUSELOGO

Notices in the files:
parts and their libraries:
microbuilder: This work is placed in the public domain, and may be freely used for commercial and non-commercial work with the following conditions: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
SparkFun-PowerSymbols: Licensing: Creative Commons ShareAlike 4.0 International - https://creativecommons.org/licenses/by-sa/4.0
